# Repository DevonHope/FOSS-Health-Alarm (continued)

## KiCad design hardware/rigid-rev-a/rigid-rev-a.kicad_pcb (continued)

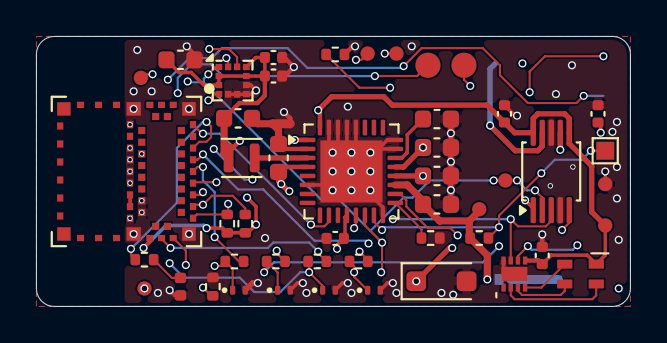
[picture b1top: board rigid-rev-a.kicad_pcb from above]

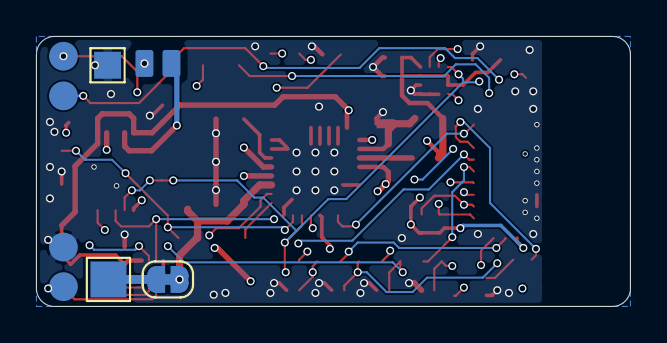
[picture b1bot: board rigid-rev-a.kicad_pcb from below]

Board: 4 copper layers, 33.0 x 15.0 mm, 53 parts (5 on the bottom side), 36 nets.

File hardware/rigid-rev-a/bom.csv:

"Comment","Designator","Footprint","LCSC","MPN","Qty","DNP"
"1uF 50V X5R","C201,C206","Capacitor_SMD:C_0603_1608Metric","C15849","","2",""
"2.2uF 16V X5R","C202","Capacitor_SMD:C_0603_1608Metric","C23630","","1",""
"100nF","C203,C401,C402","Capacitor_SMD:C_0402_1005Metric","C1525","","3",""
"10uF 25V X5R","C204,C205,C207,C403","Capacitor_SMD:C_0603_1608Metric","C96446","","4",""
"1uF 25V X5R","C501,C502","Capacitor_SMD:C_0402_1005Metric","C52923","","2",""
"SMF12A (TVS)","D601","Diode_SMD:D_SOD-123F","C207255","Littelfuse SMF12A","1",""
"TPD1E10B06","D602,D603,D604,D605","Package_SON:Texas_DPY0002A_0.6x1mm_P0.65mm","C48260","TI TPD1E10B06DPYR","4",""
"red DNP","D701","LED_SMD:LED_0402_1005Metric","C25503345","XINGLIGHT XL-1005SURC","1","DNP"
"2.2uH","L201","Inductor_SMD:L_Murata_DFE201610P","C337891","Murata DFE201610E-2R2M","1",""
"100k DNP","R201","Resistor_SMD:R_0402_1005Metric","C25741","","1","DNP"
"68k 1%","R202","Resistor_SMD:R_0402_1005Metric","C36871","","1",""
"4.7k","R203,R204","Resistor_SMD:R_0402_1005Metric","C25900","","2",""
"100","R601,R602,R603,R604","Resistor_SMD:R_0402_1005Metric","C25076","","4",""
"100k","R605","Resistor_SMD:R_0402_1005Metric","C25741","","1",""
"1k DNP","R701","Resistor_SMD:R_0402_1005Metric","C11702","","1","DNP"
"button DNP","SW201","Button_Switch_SMD:SW_SPST_B3U-1000P","C231329","Omron B3U-1000P","1","DNP"
"10k B3380","TH201","Resistor_SMD:R_0402_1005Metric","C77131","Murata NCP15XH103F03RC","1",""
"ISP2454-LX","U1","wakeband:InsightSiP_ISP2454_LGA-62_8x8mm","","","1",""
"nPM1304-QEAA","U201","Package_DFN_QFN:QFN-32-1EP_5x5mm_P0.5mm_EP3.45x3.45mm","","","1",""
"LIS2DW12TR","U401","Package_LGA:LGA-12_2x2mm_P0.5mm","C189624","","1",""
"DRV2605LDGSR","U501","Package_SO:TSSOP-10_3x3mm_P0.5mm","C527464","","1",""
"60mAh 3.7V protected LiPo, ~16x13x4-5 mm, wire leads (hand-soldered to TP201/TP202, not assembled; alt. Ampul 401215)","BT1 (off-board)","","","X2 Robotics 3.7V 60mAh LiPo","1","not assembled"

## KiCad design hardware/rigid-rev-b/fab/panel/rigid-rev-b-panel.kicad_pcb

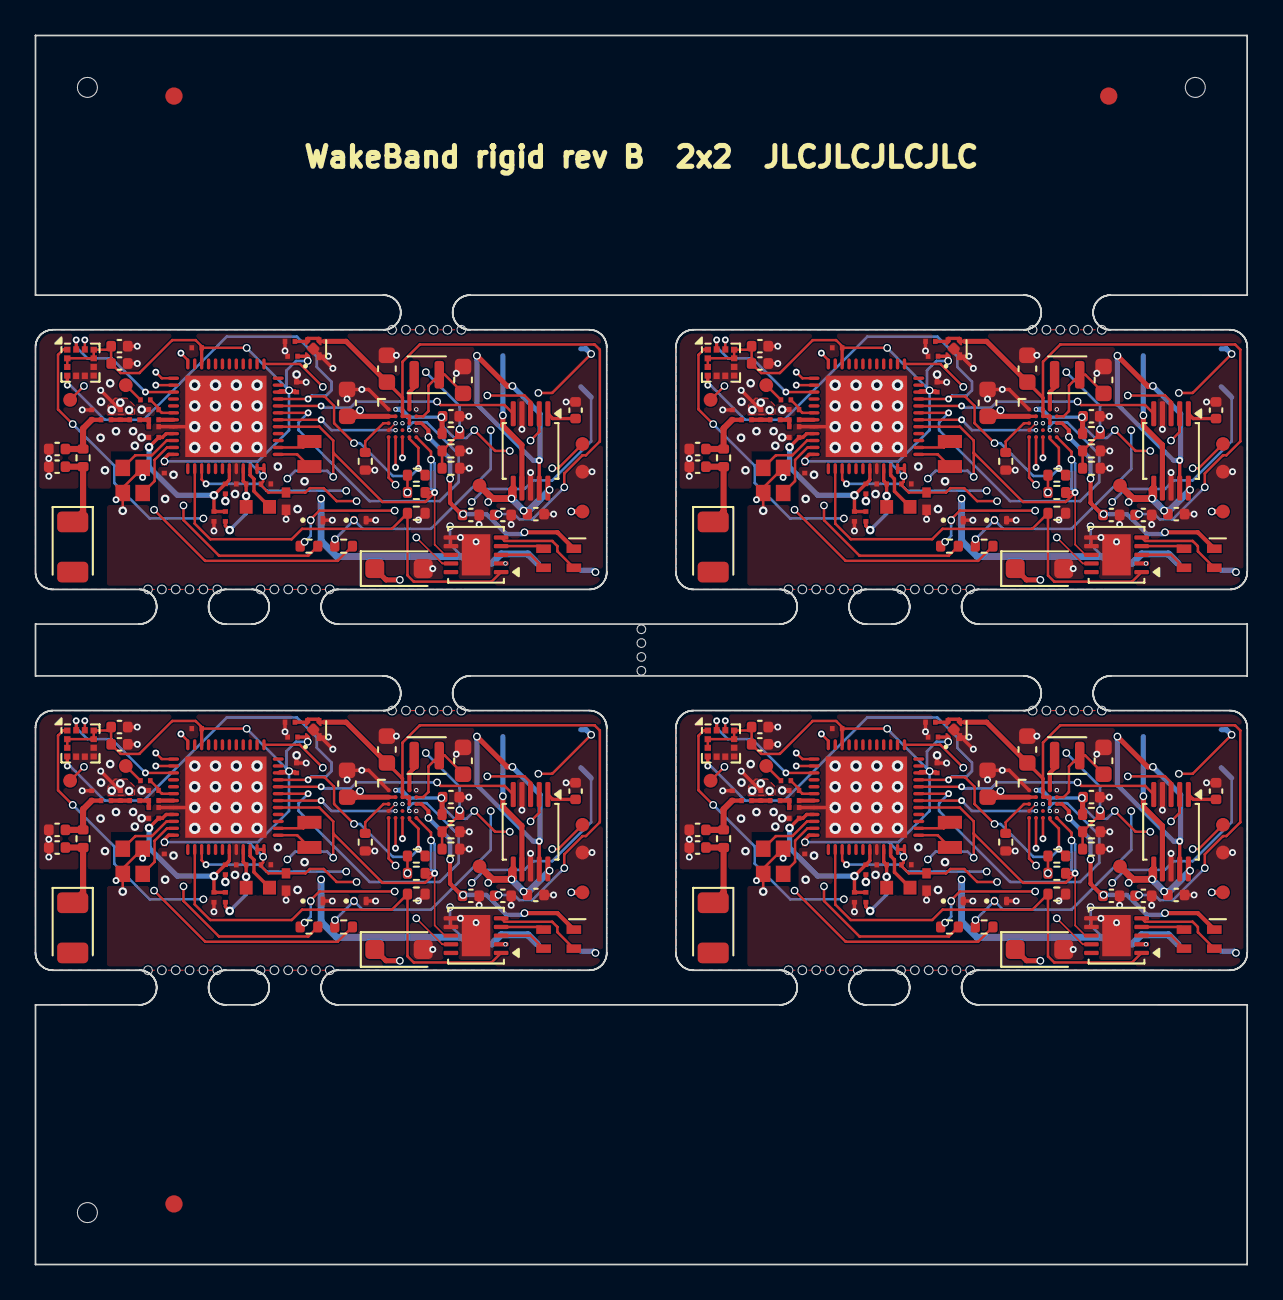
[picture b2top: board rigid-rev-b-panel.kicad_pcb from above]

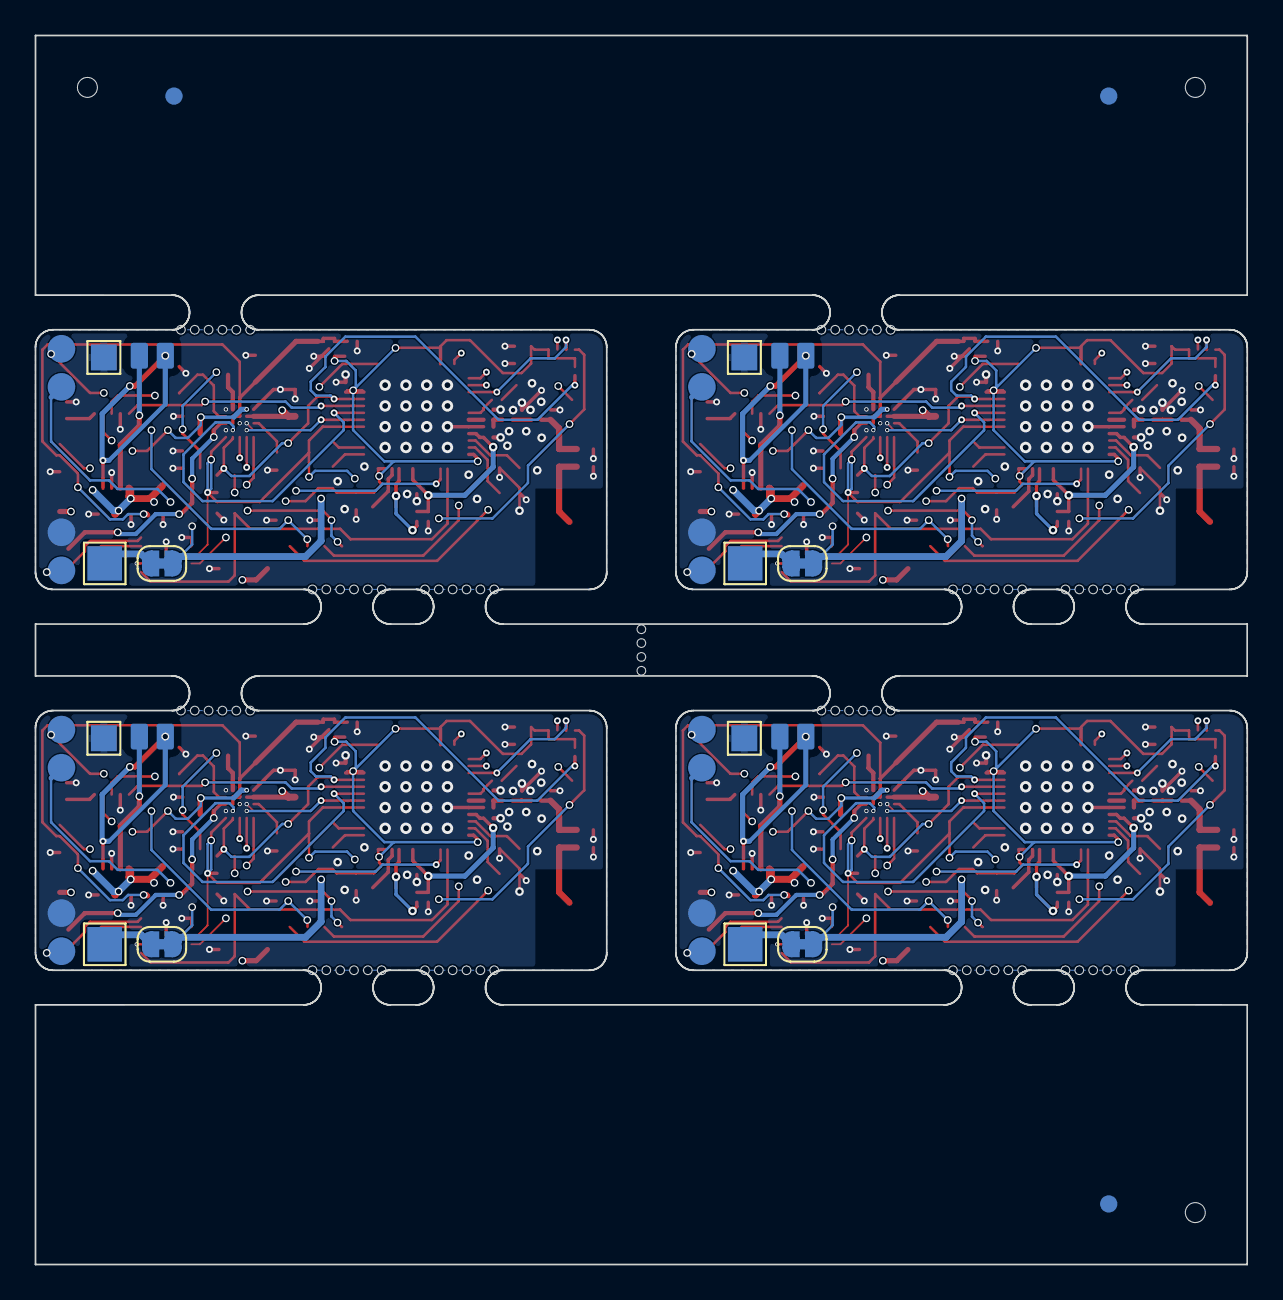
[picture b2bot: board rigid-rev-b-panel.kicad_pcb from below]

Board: 4 copper layers, 70.0 x 71.0 mm, 361 parts (23 on the bottom side), 184 nets.

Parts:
AE1_0, AE1_1, AE1_2, AE1_3: 2450AT18A0100001E; Johanson_2450AT18x100
C1_0, C1_1, C1_2, C1_3, C2_0, C2_1, C2_2, C2_3: 2.2uF; Nordic_CAPC0603X03L_C
C3_0, C3_1, C3_2, C3_3: 10uF; Nordic_CAPC1005X04L
C4_0, C4_1, C4_2, C4_3, C7_0, C7_1, C7_2, C7_3, C8_0, C8_1, C8_2, C8_3, C10_0, C10_1, C10_2, C10_3: 100nF; Nordic_CAPC0603X03L_C
C5_0, C5_1, C5_2, C5_3: 2.2nF; Nordic_CAPC0603X03L_C
C6_0, C6_1, C6_2, C6_3: 1.5pF; Nordic_CAPC0603X03L_C
C9_0, C9_1, C9_2, C9_3: 2.0pF; Nordic_CAPC0603X03L_C
C11_0, C11_1, C11_2, C11_3: 0.3pF; Nordic_CAPC0603X03L_C
C12_0, C12_1, C12_2, C12_3: 10nF; Nordic_CAPC0603X03L_C
C13_0, C13_1, C13_2, C13_3: 3.9pF; Nordic_CAPC0603X03L_C
C14_0, C14_1, C14_2, C14_3, C15_0, C15_1, C15_2, C15_3: DNP; C_0402_1005Metric
C201_0, C201_1, C201_2, C201_3, C208_0, C208_1, C208_2, C208_3, C501_0, C501_1, C501_2, C501_3, C502_0, C502_1, C502_2, C502_3: 1uF; C_0402_1005Metric
C202_0, C202_1, C202_2, C202_3: 2.2uF; C_0603_1608Metric
C205_0, C205_1, C205_2, C205_3, C206_0, C206_1, C206_2, C206_3: 10uF; C_0603_1608Metric
C209_0, C209_1, C209_2, C209_3, C401_0, C401_1, C401_2, C401_3, C402_0, C402_1, C402_2, C402_3: 100nF; C_0402_1005Metric
C210_0, C210_1, C210_2, C210_3, C211_0, C211_1, C211_2, C211_3: 1uF; Nordic_CAPC0603X03L_C
D601_0, D601_1, D601_2, D601_3: SMF12A; D_SOD-123F
D602_0, D602_1, D602_2, D602_3, D603_0, D603_1, D603_2, D603_3: TPD1E10B06; Texas_DPY0002A_0.6x1mm_P0.65mm
D702_0, D702_1, D702_2, D702_3: TJ-S1615SW6TGLCCYRGB-A5; LED_TOGIALED_1615_RGB_CommonAnode
FB1_0, FB1_1, FB1_2, FB1_3: 120R@100MHz; Nordic_INDC0603X03L_C
J601_0, J601_1, J601_2, J601_3: Dock landing pads; DockLanding_4xB_D1.6mm
JP201_0, JP201_1, JP201_2, JP201_3: I_BAT; SolderJumper-2_P1.3mm_Bridged_RoundedPad1.0x1.5mm
KiKit_FID_B_1, KiKit_FID_B_2, KiKit_FID_B_3: Fiducial
KiKit_FID_T_1, KiKit_FID_T_2, KiKit_FID_T_3: Fiducial
KiKit_MB_1_1, KiKit_MB_1_2, KiKit_MB_1_3, KiKit_MB_1_4, KiKit_MB_1_5, KiKit_MB_1_6, KiKit_MB_2_1, KiKit_MB_2_2, KiKit_MB_2_3, KiKit_MB_2_4, KiKit_MB_2_5, KiKit_MB_2_6, KiKit_MB_3_1, KiKit_MB_3_2, KiKit_MB_3_3, KiKit_MB_3_4, KiKit_MB_3_5, KiKit_MB_3_6, KiKit_MB_4_1, KiKit_MB_4_2, KiKit_MB_4_3, KiKit_MB_4_4, KiKit_MB_4_5, KiKit_MB_4_6, KiKit_MB_5_1, KiKit_MB_5_2, KiKit_MB_5_3, KiKit_MB_5_4, KiKit_MB_5_5, KiKit_MB_5_6, KiKit_MB_6_1, KiKit_MB_6_2, KiKit_MB_6_3, KiKit_MB_6_4, KiKit_MB_6_5, KiKit_MB_6_6, KiKit_MB_7_1, KiKit_MB_7_2, KiKit_MB_7_3, KiKit_MB_7_4, KiKit_MB_7_5, KiKit_MB_7_6, KiKit_MB_8_1, KiKit_MB_8_2, KiKit_MB_8_3, KiKit_MB_8_4, KiKit_MB_8_5, KiKit_MB_8_6, KiKit_MB_9_1, KiKit_MB_9_2, KiKit_MB_9_3, KiKit_MB_9_4, KiKit_MB_9_5, KiKit_MB_9_6, KiKit_MB_10_1, KiKit_MB_10_2, KiKit_MB_10_3, KiKit_MB_10_4, KiKit_MB_10_5, KiKit_MB_10_6, KiKit_MB_11_1, KiKit_MB_11_2, KiKit_MB_11_3, KiKit_MB_11_4, KiKit_MB_11_5, KiKit_MB_11_6, KiKit_MB_12_1, KiKit_MB_12_2, KiKit_MB_12_3, KiKit_MB_12_4, KiKit_MB_12_5, KiKit_MB_12_6, KiKit_MB_13_2, KiKit_MB_13_3, KiKit_MB_13_4, KiKit_MB_13_5: NPTH
KiKit_TO_1, KiKit_TO_2, KiKit_TO_3: NPTH
L1_0, L1_1, L1_2, L1_3: 4.7uH; Nordic_INDC1608X06L
L2_0, L2_1, L2_2, L2_3: 2.7nH; Nordic_INDC0603X03L_C
L3_0, L3_1, L3_2, L3_3, L4_0, L4_1, L4_2, L4_3: 3.5nH; Nordic_INDC0603X03L_C
L201_0, L201_1, L201_2, L201_3: 2.2uH; L_Murata_DFE201610P
R1_0, R1_1, R1_2, R1_3: 1k; Nordic_RESC0603X03L_C
R2_0, R2_1, R2_2, R2_3: 0R; R_0402_1005Metric
R202_0, R202_1, R202_2, R202_3: 6.65k; R_0402_1005Metric
R203_0, R203_1, R203_2, R203_3, R204_0, R204_1, R204_2, R204_3: 4.7k; R_0402_1005Metric
R207_0, R207_1, R207_2, R207_3: 14k; R_0402_1005Metric
R208_0, R208_1, R208_2, R208_3: 14.3k; R_0402_1005Metric
R211_0, R211_1, R211_2, R211_3: 100k; R_0402_1005Metric
R601_0, R601_1, R601_2, R601_3, R602_0, R602_1, R602_2, R602_3: 100; R_0402_1005Metric
TH201_0, TH201_1, TH201_2, TH201_3: 10k B3380; R_0402_1005Metric
TP201_0, TP201_1, TP201_2, TP201_3: BAT+ pad; TestPoint_Pad_2.0x2.0mm
TP202_0, TP202_1, TP202_2, TP202_3: BAT- pad; TestPoint_Pad_1.5x1.5mm
TP203_0, TP203_1, TP203_2, TP203_3: MR; TestPoint_Pad_D0.8mm
TP401_0, TP401_1, TP401_2, TP401_3: ACC_INT2; TestPoint_Pad_D0.8mm
TP501_0, TP501_1, TP501_2, TP501_3: LRA+; Pad_SMD_1.0x1.5mm
TP502_0, TP502_1, TP502_2, TP502_3: LRA-; Pad_SMD_1.0x1.5mm
TP701_0, TP701_1, TP701_2, TP701_3: nRESET; TestPoint_Pad_D0.8mm
TP705_0, TP705_1, TP705_2, TP705_3: PMID; TestPoint_Pad_D0.8mm
TP706_0, TP706_1, TP706_2, TP706_3: VBAT; TestPoint_Pad_D0.8mm
TP707_0, TP707_1, TP707_2, TP707_3: GND; TestPoint_Pad_D0.8mm
U1_0, U1_1, U1_2, U1_3: nRF54L10-QFAA; Nordic_QFN40P600X600X90-48N
U201_0, U201_1, U201_2, U201_3: BQ25125; TI_DSBGA-25_2.5x2.5mm_Layout5x5_P0.4mm
U202_0, U202_1, U202_2, U202_3: IS31FL3193; DFN-10-1EP_3x3mm_P0.5mm_EP1.65x2.38mm
U203_0, U203_1, U203_2, U203_3: TPS7A0220; Texas_X2SON-4_1x1mm_P0.65mm_SilkTrim
U401_0, U401_1, U401_2, U401_3: LIS2DW12TR; LGA-12_2x2mm_P0.5mm
U501_0, U501_1, U501_2, U501_3: DRV2605LDGSR; TSSOP-10_3x3mm_P0.5mm
X1_0, X1_1, X1_2, X1_3: 32.768kHz 9pF; Nordic_XTAL_2012
X2_0, X2_1, X2_2, X2_3: 32MHz 8pF; Nordic_BT-XTAL_2016

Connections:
Board_0-/ACC_INT1: U1_0.27, U401_0.12
Board_0-/ACC_INT2: TP401_0.1, U1_0.24, U401_0.11
Board_0-/ANT: L2_0.1, U1_0.31
Board_0-/ANT_FEED: AE1_0.1, C15_0.1, R2_0.2
Board_0-/BATT_P: JP201_0.1, TP201_0.1
Board_0-/CHG_CD: U1_0.39, U201_0.E2
Board_0-/CHG_MR: TP203_0.1, U201_0.E1
Board_0-/DCC: L1_0.1, U1_0.46
Board_0-/DECA: C2_0.2, C5_0.2, C12_0.2, FB1_0.2, U1_0.33, U1_0.43
Board_0-/DECD: C1_0.2, FB1_0.1, L1_0.2, U1_0.45
Board_0-/DOCK_PG: U1_0.7, U201_0.D4
Board_0-/GND: C1_0.1, C2_0.1, C3_0.1, C4_0.2, C5_0.1, C6_0.1, C7_0.2, C8_0.2, C9_0.1, C10_0.2, C11_0.1, C12_0.1, C13_0.1, C14_0.2, C15_0.2, C201_0.2, C202_0.2, C205_0.2, C206_0.2, C208_0.2, C209_0.2, C210_0.2, C211_0.2, C401_0.2, C402_0.2, C501_0.2, C502_0.2, D601_0.2, D602_0.2, D603_0.2, J601_0.2, R202_0.2, R208_0.2, R211_0.2, TH201_0.2, TP202_0.1, TP707_0.1, U1_0.32, U1_0.44, U1_0.49, U201_0.A1, U201_0.A5, U201_0.C2, U201_0.D1, U201_0.D5, U202_0.6, U202_0.7, U202_0.11, U203_0.2, U203_0.5, U401_0.5, U401_0.6, U401_0.7, U401_0.8, U501_0.4, U501_0.8, X2_0.2, X2_0.4
Board_0-/HAPT_EN: U1_0.8, U501_0.5
Board_0-/I2C_SCL: R204_0.2, U1_0.5, U201_0.E5, U202_0.8, U401_0.1, U501_0.2
Board_0-/I2C_SDA: R203_0.2, U1_0.9, U201_0.E4, U202_0.9, U401_0.4, U501_0.3
Board_0-/ISET: R202_0.1, U201_0.C1
Board_0-/LED_B: D702_0.2, U202_0.4
Board_0-/LED_EN: R211_0.1, U1_0.38, U202_0.1
Board_0-/LED_G: D702_0.3, U202_0.3
Board_0-/LED_R: D702_0.4, U202_0.5
Board_0-/LRA_N: TP502_0.1, U501_0.9
Board_0-/LRA_P: TP501_0.1, U501_0.7
Board_0-/LS_CTRL: U1_0.13, U201_0.E3
Board_0-/PAD_SWDCLK: D602_0.1, J601_0.3, R601_0.1
Board_0-/PAD_SWDIO: D603_0.1, J601_0.4, R602_0.1
Board_0-/PMIC_INT: U1_0.6, U201_0.D2
Board_0-/PMID: C206_0.1, C209_0.1, C210_0.1, TP705_0.1, U201_0.A3, U201_0.B3, U201_0.B4, U201_0.C4, U202_0.2, U203_0.3, U203_0.4
Board_0-/REG: C502_0.1, U501_0.1
Board_0-/RF1: C6_0.2, L2_0.2, L3_0.1
Board_0-/RF2: C9_0.2, L3_0.2, L4_0.1
Board_0-/RF_50: C11_0.2, C14_0.1, L4_0.2, R2_0.1
Board_0-/SW: L201_0.1, U201_0.A4
Board_0-/SWDCLK: R601_0.2, U1_0.26
Board_0-/SWDIO: R602_0.2, U1_0.25
Board_0-/TS: R207_0.2, R208_0.1, TH201_0.1, U201_0.C3
Board_0-/VBAT: C202_0.1, C501_0.1, JP201_0.2, TP706_0.1, U201_0.B1, U201_0.B2, U501_0.6, U501_0.10
Board_0-/VDD_2V0: C3_0.2, C4_0.1, C7_0.1, C8_0.1, C10_0.1, C211_0.1, C401_0.1, C402_0.1, R203_0.1, R204_0.1, U1_0.10, U1_0.22, U1_0.36, U1_0.47, U1_0.48, U203_0.1, U401_0.2, U401_0.3, U401_0.9, U401_0.10
Board_0-/VIN: C201_0.1, D601_0.1, J601_0.1, R207_0.1, U201_0.A2
Board_0-/VLED: C208_0.1, D702_0.1, U201_0.C5
Board_0-/VSYS: C205_0.1, L201_0.2, U201_0.B5
Board_0-/XC1: U1_0.34, X2_0.1
Board_0-/XC2: U1_0.35, X2_0.3
Board_0-/XL1: U1_0.1, X1_0.2
Board_0-/XL2: U1_0.2, X1_0.1
Board_0-/nRESET: R1_0.2, TP701_0.1
Board_0-/nRESET_IC: C13_0.2, R1_0.1, U1_0.30
Board_1-/ACC_INT1: U1_1.27, U401_1.12
Board_1-/ACC_INT2: TP401_1.1, U1_1.24, U401_1.11
Board_1-/ANT: L2_1.1, U1_1.31
Board_1-/ANT_FEED: AE1_1.1, C15_1.1, R2_1.2
Board_1-/BATT_P: JP201_1.1, TP201_1.1
Board_1-/CHG_CD: U1_1.39, U201_1.E2
Board_1-/CHG_MR: TP203_1.1, U201_1.E1
Board_1-/DCC: L1_1.1, U1_1.46
Board_1-/DECA: C2_1.2, C5_1.2, C12_1.2, FB1_1.2, U1_1.33, U1_1.43
Board_1-/DECD: C1_1.2, FB1_1.1, L1_1.2, U1_1.45
Board_1-/DOCK_PG: U1_1.7, U201_1.D4
Board_1-/GND: C1_1.1, C2_1.1, C3_1.1, C4_1.2, C5_1.1, C6_1.1, C7_1.2, C8_1.2, C9_1.1, C10_1.2, C11_1.1, C12_1.1, C13_1.1, C14_1.2, C15_1.2, C201_1.2, C202_1.2, C205_1.2, C206_1.2, C208_1.2, C209_1.2, C210_1.2, C211_1.2, C401_1.2, C402_1.2, C501_1.2, C502_1.2, D601_1.2, D602_1.2, D603_1.2, J601_1.2, R202_1.2, R208_1.2, R211_1.2, TH201_1.2, TP202_1.1, TP707_1.1, U1_1.32, U1_1.44, U1_1.49, U201_1.A1, U201_1.A5, U201_1.C2, U201_1.D1, U201_1.D5, U202_1.6, U202_1.7, U202_1.11, U203_1.2, U203_1.5, U401_1.5, U401_1.6, U401_1.7, U401_1.8, U501_1.4, U501_1.8, X2_1.2, X2_1.4
Board_1-/HAPT_EN: U1_1.8, U501_1.5
Board_1-/I2C_SCL: R204_1.2, U1_1.5, U201_1.E5, U202_1.8, U401_1.1, U501_1.2
Board_1-/I2C_SDA: R203_1.2, U1_1.9, U201_1.E4, U202_1.9, U401_1.4, U501_1.3
Board_1-/ISET: R202_1.1, U201_1.C1
Board_1-/LED_B: D702_1.2, U202_1.4
Board_1-/LED_EN: R211_1.1, U1_1.38, U202_1.1
Board_1-/LED_G: D702_1.3, U202_1.3
Board_1-/LED_R: D702_1.4, U202_1.5
Board_1-/LRA_N: TP502_1.1, U501_1.9
Board_1-/LRA_P: TP501_1.1, U501_1.7
Board_1-/LS_CTRL: U1_1.13, U201_1.E3
Board_1-/PAD_SWDCLK: D602_1.1, J601_1.3, R601_1.1
Board_1-/PAD_SWDIO: D603_1.1, J601_1.4, R602_1.1
Board_1-/PMIC_INT: U1_1.6, U201_1.D2
Board_1-/PMID: C206_1.1, C209_1.1, C210_1.1, TP705_1.1, U201_1.A3, U201_1.B3, U201_1.B4, U201_1.C4, U202_1.2, U203_1.3, U203_1.4
Board_1-/REG: C502_1.1, U501_1.1
Board_1-/RF1: C6_1.2, L2_1.2, L3_1.1
Board_1-/RF2: C9_1.2, L3_1.2, L4_1.1
Board_1-/RF_50: C11_1.2, C14_1.1, L4_1.2, R2_1.1
Board_1-/SW: L201_1.1, U201_1.A4
Board_1-/SWDCLK: R601_1.2, U1_1.26
Board_1-/SWDIO: R602_1.2, U1_1.25
Board_1-/TS: R207_1.2, R208_1.1, TH201_1.1, U201_1.C3
Board_1-/VBAT: C202_1.1, C501_1.1, JP201_1.2, TP706_1.1, U201_1.B1, U201_1.B2, U501_1.6, U501_1.10
Board_1-/VDD_2V0: C3_1.2, C4_1.1, C7_1.1, C8_1.1, C10_1.1, C211_1.1, C401_1.1, C402_1.1, R203_1.1, R204_1.1, U1_1.10, U1_1.22, U1_1.36, U1_1.47, U1_1.48, U203_1.1, U401_1.2, U401_1.3, U401_1.9, U401_1.10
Board_1-/VIN: C201_1.1, D601_1.1, J601_1.1, R207_1.1, U201_1.A2
Board_1-/VLED: C208_1.1, D702_1.1, U201_1.C5
Board_1-/VSYS: C205_1.1, L201_1.2, U201_1.B5
Board_1-/XC1: U1_1.34, X2_1.1
Board_1-/XC2: U1_1.35, X2_1.3
Board_1-/XL1: U1_1.1, X1_1.2
Board_1-/XL2: U1_1.2, X1_1.1
Board_1-/nRESET: R1_1.2, TP701_1.1
Board_1-/nRESET_IC: C13_1.2, R1_1.1, U1_1.30
Board_2-/ACC_INT1: U1_2.27, U401_2.12
Board_2-/ACC_INT2: TP401_2.1, U1_2.24, U401_2.11
Board_2-/ANT: L2_2.1, U1_2.31
Board_2-/ANT_FEED: AE1_2.1, C15_2.1, R2_2.2
Board_2-/BATT_P: JP201_2.1, TP201_2.1
Board_2-/CHG_CD: U1_2.39, U201_2.E2
Board_2-/CHG_MR: TP203_2.1, U201_2.E1
Board_2-/DCC: L1_2.1, U1_2.46
Board_2-/DECA: C2_2.2, C5_2.2, C12_2.2, FB1_2.2, U1_2.33, U1_2.43
Board_2-/DECD: C1_2.2, FB1_2.1, L1_2.2, U1_2.45
Board_2-/DOCK_PG: U1_2.7, U201_2.D4
Board_2-/GND: C1_2.1, C2_2.1, C3_2.1, C4_2.2, C5_2.1, C6_2.1, C7_2.2, C8_2.2, C9_2.1, C10_2.2, C11_2.1, C12_2.1, C13_2.1, C14_2.2, C15_2.2, C201_2.2, C202_2.2, C205_2.2, C206_2.2, C208_2.2, C209_2.2, C210_2.2, C211_2.2, C401_2.2, C402_2.2, C501_2.2, C502_2.2, D601_2.2, D602_2.2, D603_2.2, J601_2.2, R202_2.2, R208_2.2, R211_2.2, TH201_2.2, TP202_2.1, TP707_2.1, U1_2.32, U1_2.44, U1_2.49, U201_2.A1, U201_2.A5, U201_2.C2, U201_2.D1, U201_2.D5, U202_2.6, U202_2.7, U202_2.11, U203_2.2, U203_2.5, U401_2.5, U401_2.6, U401_2.7, U401_2.8, U501_2.4, U501_2.8, X2_2.2, X2_2.4
Board_2-/HAPT_EN: U1_2.8, U501_2.5
Board_2-/I2C_SCL: R204_2.2, U1_2.5, U201_2.E5, U202_2.8, U401_2.1, U501_2.2
Board_2-/I2C_SDA: R203_2.2, U1_2.9, U201_2.E4, U202_2.9, U401_2.4, U501_2.3
Board_2-/ISET: R202_2.1, U201_2.C1
Board_2-/LED_B: D702_2.2, U202_2.4
Board_2-/LED_EN: R211_2.1, U1_2.38, U202_2.1
Board_2-/LED_G: D702_2.3, U202_2.3
Board_2-/LED_R: D702_2.4, U202_2.5
Board_2-/LRA_N: TP502_2.1, U501_2.9
Board_2-/LRA_P: TP501_2.1, U501_2.7
Board_2-/LS_CTRL: U1_2.13, U201_2.E3
Board_2-/PAD_SWDCLK: D602_2.1, J601_2.3, R601_2.1
Board_2-/PAD_SWDIO: D603_2.1, J601_2.4, R602_2.1
Board_2-/PMIC_INT: U1_2.6, U201_2.D2
Board_2-/PMID: C206_2.1, C209_2.1, C210_2.1, TP705_2.1, U201_2.A3, U201_2.B3, U201_2.B4, U201_2.C4, U202_2.2, U203_2.3, U203_2.4
Board_2-/REG: C502_2.1, U501_2.1
Board_2-/RF1: C6_2.2, L2_2.2, L3_2.1
Board_2-/RF2: C9_2.2, L3_2.2, L4_2.1
Board_2-/RF_50: C11_2.2, C14_2.1, L4_2.2, R2_2.1
Board_2-/SW: L201_2.1, U201_2.A4
Board_2-/SWDCLK: R601_2.2, U1_2.26
Board_2-/SWDIO: R602_2.2, U1_2.25
Board_2-/TS: R207_2.2, R208_2.1, TH201_2.1, U201_2.C3
Board_2-/VBAT: C202_2.1, C501_2.1, JP201_2.2, TP706_2.1, U201_2.B1, U201_2.B2, U501_2.6, U501_2.10
Board_2-/VDD_2V0: C3_2.2, C4_2.1, C7_2.1, C8_2.1, C10_2.1, C211_2.1, C401_2.1, C402_2.1, R203_2.1, R204_2.1, U1_2.10, U1_2.22, U1_2.36, U1_2.47, U1_2.48, U203_2.1, U401_2.2, U401_2.3, U401_2.9, U401_2.10
Board_2-/VIN: C201_2.1, D601_2.1, J601_2.1, R207_2.1, U201_2.A2
Board_2-/VLED: C208_2.1, D702_2.1, U201_2.C5
Board_2-/VSYS: C205_2.1, L201_2.2, U201_2.B5
Board_2-/XC1: U1_2.34, X2_2.1
Board_2-/XC2: U1_2.35, X2_2.3
Board_2-/XL1: U1_2.1, X1_2.2
Board_2-/XL2: U1_2.2, X1_2.1
Board_2-/nRESET: R1_2.2, TP701_2.1
Board_2-/nRESET_IC: C13_2.2, R1_2.1, U1_2.30
Board_3-/ACC_INT1: U1_3.27, U401_3.12
Board_3-/ACC_INT2: TP401_3.1, U1_3.24, U401_3.11
Board_3-/ANT: L2_3.1, U1_3.31
Board_3-/ANT_FEED: AE1_3.1, C15_3.1, R2_3.2
Board_3-/BATT_P: JP201_3.1, TP201_3.1
Board_3-/CHG_CD: U1_3.39, U201_3.E2
Board_3-/CHG_MR: TP203_3.1, U201_3.E1
Board_3-/DCC: L1_3.1, U1_3.46
Board_3-/DECA: C2_3.2, C5_3.2, C12_3.2, FB1_3.2, U1_3.33, U1_3.43
Board_3-/DECD: C1_3.2, FB1_3.1, L1_3.2, U1_3.45
Board_3-/DOCK_PG: U1_3.7, U201_3.D4
Board_3-/GND: C1_3.1, C2_3.1, C3_3.1, C4_3.2, C5_3.1, C6_3.1, C7_3.2, C8_3.2, C9_3.1, C10_3.2, C11_3.1, C12_3.1, C13_3.1, C14_3.2, C15_3.2, C201_3.2, C202_3.2, C205_3.2, C206_3.2, C208_3.2, C209_3.2, C210_3.2, C211_3.2, C401_3.2, C402_3.2, C501_3.2, C502_3.2, D601_3.2, D602_3.2, D603_3.2, J601_3.2, R202_3.2, R208_3.2, R211_3.2, TH201_3.2, TP202_3.1, TP707_3.1, U1_3.32, U1_3.44, U1_3.49, U201_3.A1, U201_3.A5, U201_3.C2, U201_3.D1, U201_3.D5, U202_3.6, U202_3.7, U202_3.11, U203_3.2, U203_3.5, U401_3.5, U401_3.6, U401_3.7, U401_3.8, U501_3.4, U501_3.8, X2_3.2, X2_3.4
Board_3-/HAPT_EN: U1_3.8, U501_3.5
Board_3-/I2C_SCL: R204_3.2, U1_3.5, U201_3.E5, U202_3.8, U401_3.1, U501_3.2
Board_3-/I2C_SDA: R203_3.2, U1_3.9, U201_3.E4, U202_3.9, U401_3.4, U501_3.3
Board_3-/ISET: R202_3.1, U201_3.C1
Board_3-/LED_B: D702_3.2, U202_3.4
Board_3-/LED_EN: R211_3.1, U1_3.38, U202_3.1
Board_3-/LED_G: D702_3.3, U202_3.3
Board_3-/LED_R: D702_3.4, U202_3.5
Board_3-/LRA_N: TP502_3.1, U501_3.9
Board_3-/LRA_P: TP501_3.1, U501_3.7
Board_3-/LS_CTRL: U1_3.13, U201_3.E3
Board_3-/PAD_SWDCLK: D602_3.1, J601_3.3, R601_3.1
Board_3-/PAD_SWDIO: D603_3.1, J601_3.4, R602_3.1
Board_3-/PMIC_INT: U1_3.6, U201_3.D2
Board_3-/PMID: C206_3.1, C209_3.1, C210_3.1, TP705_3.1, U201_3.A3, U201_3.B3, U201_3.B4, U201_3.C4, U202_3.2, U203_3.3, U203_3.4
Board_3-/REG: C502_3.1, U501_3.1
Board_3-/RF1: C6_3.2, L2_3.2, L3_3.1
Board_3-/RF2: C9_3.2, L3_3.2, L4_3.1
Board_3-/RF_50: C11_3.2, C14_3.1, L4_3.2, R2_3.1
Board_3-/SW: L201_3.1, U201_3.A4
Board_3-/SWDCLK: R601_3.2, U1_3.26
Board_3-/SWDIO: R602_3.2, U1_3.25
Board_3-/TS: R207_3.2, R208_3.1, TH201_3.1, U201_3.C3
Board_3-/VBAT: C202_3.1, C501_3.1, JP201_3.2, TP706_3.1, U201_3.B1, U201_3.B2, U501_3.6, U501_3.10
Board_3-/VDD_2V0: C3_3.2, C4_3.1, C7_3.1, C8_3.1, C10_3.1, C211_3.1, C401_3.1, C402_3.1, R203_3.1, R204_3.1, U1_3.10, U1_3.22, U1_3.36, U1_3.47, U1_3.48, U203_3.1, U401_3.2, U401_3.3, U401_3.9, U401_3.10
Board_3-/VIN: C201_3.1, D601_3.1, J601_3.1, R207_3.1, U201_3.A2
Board_3-/VLED: C208_3.1, D702_3.1, U201_3.C5
Board_3-/VSYS: C205_3.1, L201_3.2, U201_3.B5
Board_3-/XC1: U1_3.34, X2_3.1
Board_3-/XC2: U1_3.35, X2_3.3
Board_3-/XL1: U1_3.1, X1_3.2
Board_3-/XL2: U1_3.2, X1_3.1
Board_3-/nRESET: R1_3.2, TP701_3.1
Board_3-/nRESET_IC: C13_3.2, R1_3.1, U1_3.30
